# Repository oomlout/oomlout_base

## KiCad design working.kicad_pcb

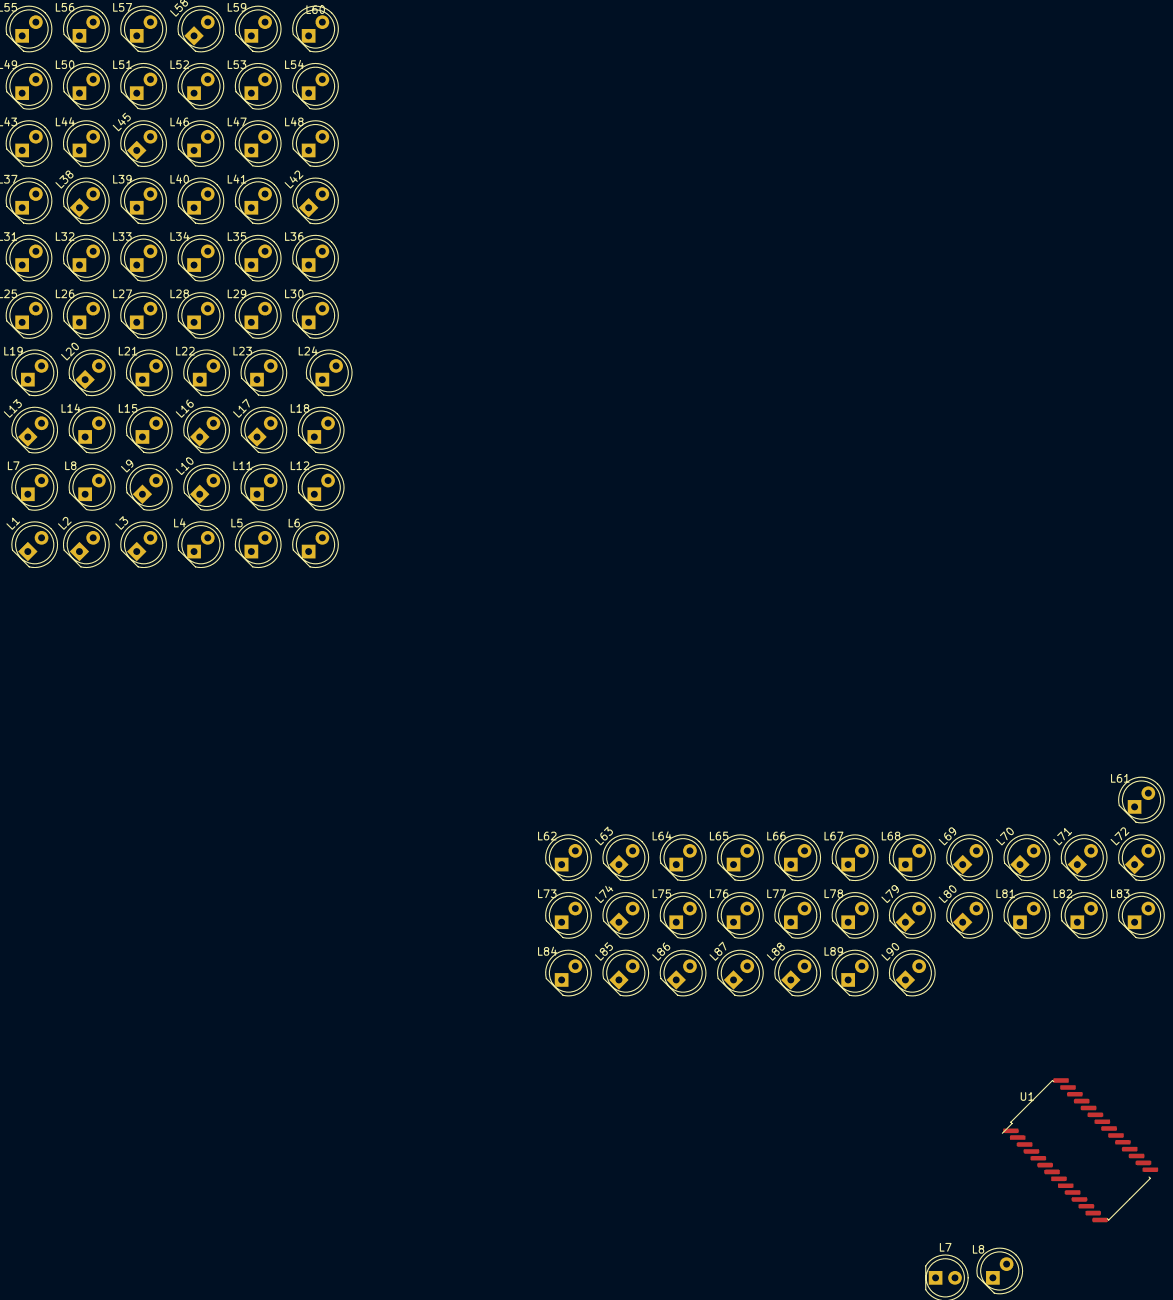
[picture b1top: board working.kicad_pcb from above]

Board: 2 copper layers, 93 parts (0 on the bottom side), 23 nets, no tracks yet.

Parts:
L1, L2, L3, L4, L5, L6, L7, L7#2, L8, L8#2, L9, L10, L11, L12, L13, L14, L15, L16, L17, L18, L19, L20, L21, L22, L23, L24, L25, L26, L27, L28, L29, L30, L31, L32, L33, L34, L35, L36, L37, L38, L39, L40, L41, L42, L43, L44, L45, L46, L47, L48, L49, L50, L51, L52, L53, L54, L55, L56, L57, L58, L59, L60, L61, L62, L63, L64, L65, L66, L67, L68, L69, L70, L71, L72, L73, L74, L75, L76, L77, L78, L79, L80, L81, L82, L83, L84, L85, L86, L87, L88, L89, L90: l5_electronic_led_5_mm; l5_7297cd_electronic_led_5_mm
U1: iaip1640_electronic_ic_soic_28_wide_led_matrix_dr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; iaip1640_fe0f02_electronic_ic_soic_28_wide_led_matrix_drive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

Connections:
/col_1: L1.1 (K), L2.1 (K), L3.1 (K), L4.1 (K), L5.1 (K), L6.1 (K), L7.1 (K), L8.1 (K), U1.18 (___grid1)
/col_2: L7#2.1 (K), L8#2.1 (K), L9.1 (K), L10.1 (K), L11.1 (K), L12.1 (K), U1.19 (___grid2)
/col_3: L13.1 (K), L14.1 (K), L15.1 (K), L16.1 (K), L17.1 (K), L18.1 (K), U1.20 (___grid3)
/col_4: L19.1 (K), L20.1 (K), L21.1 (K), L22.1 (K), L23.1 (K), L24.1 (K), U1.21 (___grid4)
/col_5: L25.1 (K), L26.1 (K), L27.1 (K), L28.1 (K), L29.1 (K), L30.1 (K), U1.22 (___grid5)
/col_6: L31.1 (K), L32.1 (K), L33.1 (K), L34.1 (K), L35.1 (K), L36.1 (K), U1.23 (___grid6)
/col_7: L37.1 (K), L38.1 (K), L39.1 (K), L40.1 (K), L41.1 (K), L42.1 (K), U1.24 (___grid7)
/col_8: L43.1 (K), L44.1 (K), L45.1 (K), L46.1 (K), L47.1 (K), L48.1 (K), U1.25 (___grid8)
/col_9: L49.1 (K), L50.1 (K), L51.1 (K), L52.1 (K), L53.1 (K), L54.1 (K), U1.26 (___grid9)
/col_10: L55.1 (K), L56.1 (K), L57.1 (K), L58.1 (K), L59.1 (K), L60.1 (K), U1.27 (___grid10)
/col_11: L61.1 (K), L62.1 (K), L63.1 (K), L64.1 (K), L65.1 (K), L66.1 (K), U1.28 (___grid11)
/col_12: L67.1 (K), L68.1 (K), L69.1 (K), L70.1 (K), L71.1 (K), L72.1 (K), U1.1 (___grid12)
/col_13: L73.1 (K), L74.1 (K), L75.1 (K), L76.1 (K), L77.1 (K), L78.1 (K), U1.2 (___grid13)
/col_14: L79.1 (K), L80.1 (K), L81.1 (K), L82.1 (K), L83.1 (K), L84.1 (K), U1.3 (___grid14)
/col_15: L85.1 (K), L86.1 (K), L87.1 (K), L88.1 (K), L89.1 (K), L90.1 (K), U1.4 (___grid15)
/eg8: L8.2 (A), U1.16 (___seg8)
/row_1: L1.2 (A), L7#2.2 (A), L13.2 (A), L19.2 (A), L25.2 (A), L31.2 (A), L37.2 (A), L43.2 (A), L49.2 (A), L55.2 (A), L61.2 (A), L67.2 (A), L73.2 (A), L79.2 (A), L85.2 (A), U1.9 (___seg1)
/row_2: L2.2 (A), L8#2.2 (A), L14.2 (A), L20.2 (A), L26.2 (A), L32.2 (A), L38.2 (A), L44.2 (A), L50.2 (A), L56.2 (A), L62.2 (A), L68.2 (A), L74.2 (A), L80.2 (A), L86.2 (A), U1.10 (___seg2)
/row_3: L3.2 (A), L9.2 (A), L15.2 (A), L21.2 (A), L27.2 (A), L33.2 (A), L39.2 (A), L45.2 (A), L51.2 (A), L57.2 (A), L63.2 (A), L69.2 (A), L75.2 (A), L81.2 (A), L87.2 (A), U1.11 (___seg3)
/row_4: L4.2 (A), L10.2 (A), L16.2 (A), L22.2 (A), L28.2 (A), L34.2 (A), L40.2 (A), L46.2 (A), L52.2 (A), L58.2 (A), L64.2 (A), L70.2 (A), L76.2 (A), L82.2 (A), L88.2 (A), U1.12 (___seg4)
/row_5: L5.2 (A), L11.2 (A), L17.2 (A), L23.2 (A), L29.2 (A), L35.2 (A), L41.2 (A), L47.2 (A), L53.2 (A), L59.2 (A), L65.2 (A), L71.2 (A), L77.2 (A), L83.2 (A), L89.2 (A), U1.13 (___seg5)
/row_6: L6.2 (A), L12.2 (A), L18.2 (A), L24.2 (A), L30.2 (A), L36.2 (A), L42.2 (A), L48.2 (A), L54.2 (A), L60.2 (A), L66.2 (A), L72.2 (A), L78.2 (A), L84.2 (A), L90.2 (A), U1.14 (___seg6)
/row_7: L7.2 (A), U1.15 (___seg7)

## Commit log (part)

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2023-08-02 workigns
2023-08-02 workings.
2023-08-03 added template and push to git
2023-08-03 fixed file check
2023-08-03 added a counter return
2023-08-03 added counter
2023-08-04 fixed git approach
2023-08-04 added yaml to readme
2023-08-05 fixed an error in eagle conversion
2023-08-05 changed delay
2023-08-05 added image scaling
2023-08-05 fixing up symbol renaming
2023-08-07 added corel gen and quick git batch
2023-08-09 added comment abilty to git_all
2023-08-11 added setting repo to git push
2023-08-11 fixes
2023-08-16 fixed up repo stuff
2023-08-18 added select computer type
2023-08-20 a few changes
2023-08-21 added base corel template
2023-08-22 added svg tools
2023-08-23 added templates to pythonpip
2023-08-24 added dpi to png export
2023-08-26 fixwed up surface mouse points
2023-08-29 merging
2023-09-01 added gitgnore details
2023-09-01 added some templates
2023-09-01 added oom_git
2023-09-03 added feedback to image_resolution
2023-09-03 fixed image resolution return
2023-09-03 workigns.
2023-09-03 some working
2023-09-03 current_state
2023-09-03 added a commit py
2023-09-04 added error correction to schematic capture.
2023-09-05 added mouse move
2023-09-07 added usb switch
2023-09-07 fixings
2023-09-08 workings
2023-09-11 mrged
2023-09-12 template work
2023-09-13 worked on the error messages
2023-09-13 all fixed
2023-09-17 added symbol computer choice
2023-09-17 fixed up template and others
2023-09-20 worklibng
2023-09-20 fixed
2023-09-21 working
2023-09-22 added a test spot
2023-09-22 made better
2023-09-23 fixups
2023-09-29 overwrite addition
2023-10-04 project stuff
2023-10-08 fixed up
2023-10-08 added openscad workspace attempt
2023-10-08 readme work
2023-10-13 development pause
2023-10-15 working on things
2023-10-29 bit of work on teardown template
2023-10-29 added generate resolution
2023-11-19 added image debuig line
2023-11-20 teardown work
2023-11-24 details
2023-12-04 template working
2023-12-06 added missing only
2023-12-06 updated generate
2023-12-06 fixed overwrite settings
2023-12-06 fixed comments
2023-12-07 a few fix ups
2024-01-01 workign on new project
2024-01-04 added make_scad
2024-02-02 added a teardown check
2024-02-02 works
2024-02-02 added pcb to teardown
2024-02-20 moved to print pdf
2024-02-20 fixed image position in readme template
2024-03-11 added oomp builder option
2024-03-13 added some defaults
2024-03-19 new computer fix
2024-03-20 some work
2024-05-26 added yaml folder to base project
2024-06-23 fixed template xlsx
2024-07-08 excel stuff
2024-07-15 added accounting template
2024-07-16 switched scad running
2024-07-21 up0dated new computer process
2024-08-18 fixed error handling
2024-08-18 fix up
2024-08-21 current state
2024-08-31 added open up after creation
2024-08-31 updated scad.py
2024-10-03 label template fix
2024-10-03 label to content
2024-10-06 fixed backslash
2024-10-17 fixed defaults
2024-10-29 added messy
2024-11-04 changed xlsx file name
2024-11-11 added qrcode library
2024-11-11 added qr_code generation to configuration
2024-11-11 added python pdf
2024-11-16 added navigation to scad
2024-11-16 added yaml
2024-11-26 pipdate!
2024-11-26 added overwrite
2024-11-26 added popping save type
2024-11-29 a bit
2024-12-01 fixup
2024-12-03 fixed default oomp
2024-12-04 tweaks
2024-12-16 batch file adding
2024-12-18 batch file update
2024-12-27 added ai launch
2024-12-27 updated ai
2024-12-27 adde dopening output directories
2024-12-30 commented out oolc lines in ollc_prodiution
2025-01-09 Base
2025-09-29 changes!
2025-10-26 added ai_robo click
2026-01-08 moved story
2026-02-03 template update
2026-02-23 startup shift
2026-03-14 added music
2026-04-05 some thigns
